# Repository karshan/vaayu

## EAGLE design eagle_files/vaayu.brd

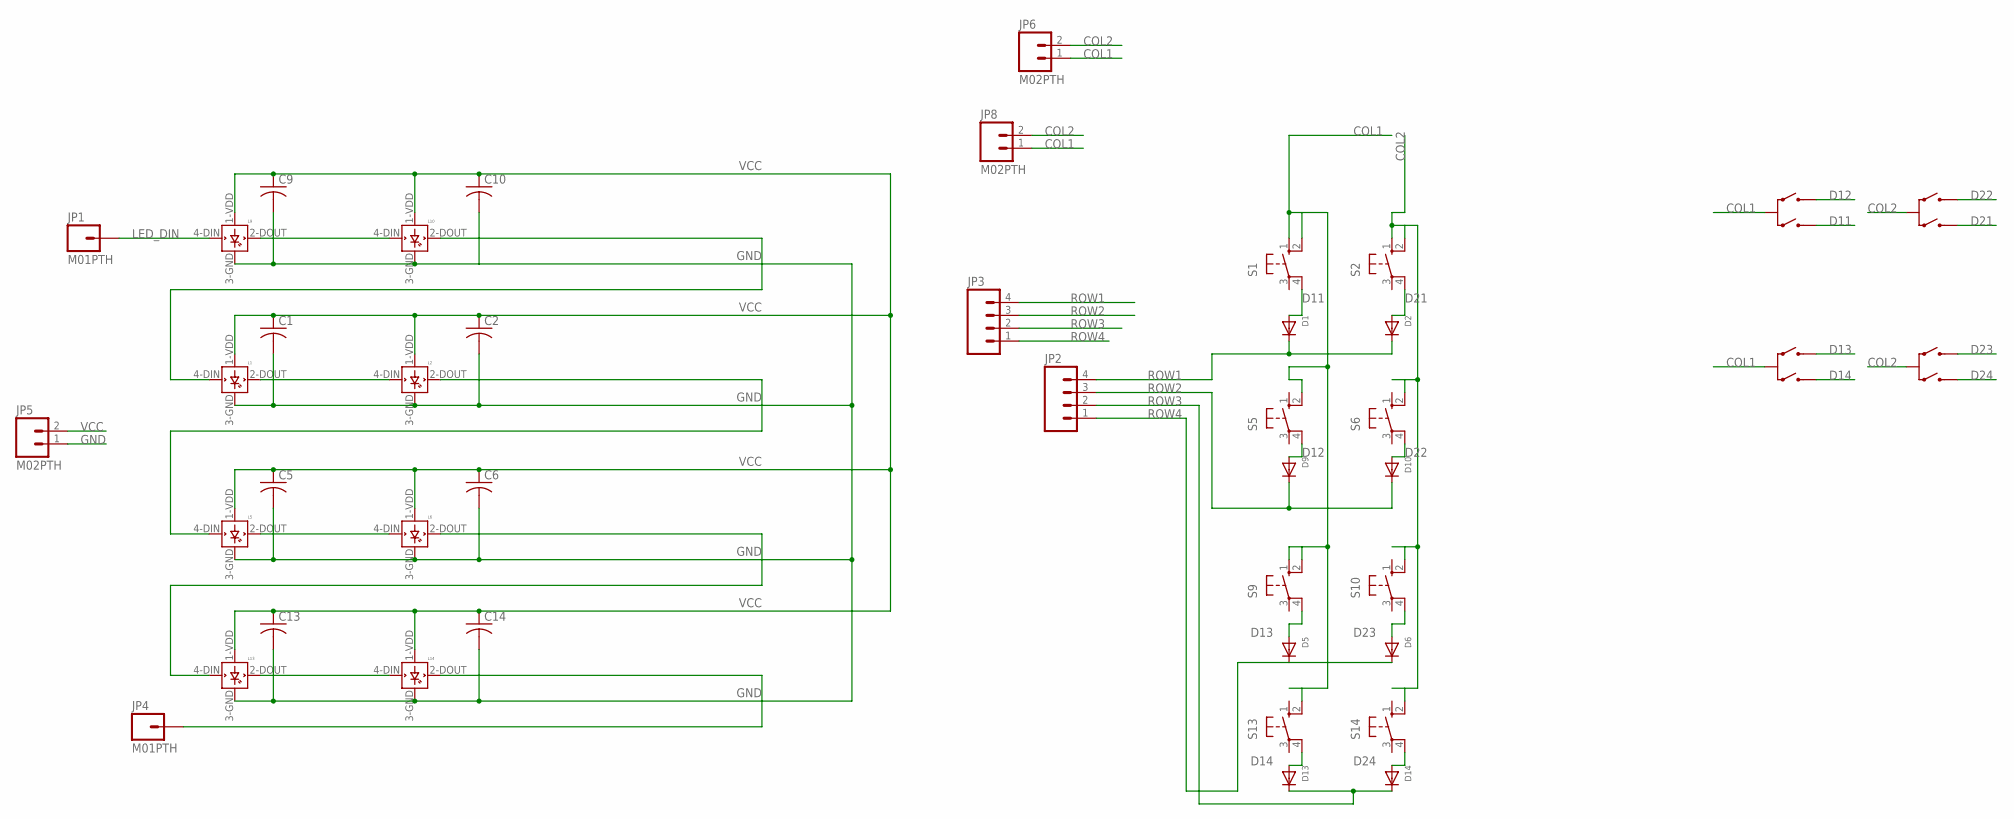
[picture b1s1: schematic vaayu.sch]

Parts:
C1, C2, C5, C6, C9, C10, C13, C14: C-USC1206; C1206
D1, D2, D5, D6, D9, D10, D13, D14: DIODESOD-123; SOD-123
JP1, JP4: M01PTH; 1X01
JP2, JP3: M04PTH; 1X04
JP5, JP6, JP8: M02PTH; 1X02
L1, L2, L5, L6, L9, L10, L13, L14: WS2812B
S1, S2, S5, S6, S9, S10, S13, S14: 10-XX; B3F-10XX
U$1, U$4, U$5, U$8: ALPHA-ROT-ENCODER; TW-700198

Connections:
COL1: JP6.1, JP8.1, S1.1 (S), S1.2 (S1), S5.2 (S1), S9.1 (S), S9.2 (S1), S13.2 (S1), U$4.P2 (COM), U$8.P2 (COM)
COL2: JP6.2, JP8.2, S2.1 (S), S2.2 (S1), S6.2 (S1), S10.2 (S1), S14.2 (S1), U$1.P2 (COM), U$5.P2 (COM)
D11: D1.A, S1.4 (P1), U$4.P1 (B)
D12: D9.A, S5.4 (P1), U$4.P3 (A)
D13: D5.A, S9.4 (P1), U$8.P3 (A)
D14: D13.A, S13.4 (P1), U$8.P1 (B)
D21: D2.A, S2.4 (P1), U$1.P1 (B)
D22: D10.A, S6.4 (P1), U$1.P3 (A)
D23: D6.A, S10.4 (P1), U$5.P3 (A)
D24: D14.A, S14.4 (P1), U$5.P1 (B)
GND: C1.2, C2.2, C5.2, C6.2, C9.2, C10.2, C13.2, C14.2, JP5.1, L1.3-GND (GND), L2.3-GND (GND), L5.3-GND (GND), L6.3-GND (GND), L9.3-GND (GND), L10.3-GND (GND), L13.3-GND (GND), L14.3-GND (GND)
LED_DIN: JP1.1, L9.4-DIN (DIN)
unnamed: L1.2-DOUT (DOUT), L2.4-DIN (DIN)
unnamed: L2.2-DOUT (DOUT), L5.4-DIN (DIN)
unnamed: L5.2-DOUT (DOUT), L6.4-DIN (DIN)
unnamed: L6.2-DOUT (DOUT), L13.4-DIN (DIN)
unnamed: L13.2-DOUT (DOUT), L14.4-DIN (DIN)
unnamed: JP4.1, L14.2-DOUT (DOUT)
unnamed: L9.2-DOUT (DOUT), L10.4-DIN (DIN)
unnamed: L1.4-DIN (DIN), L10.2-DOUT (DOUT)
ROW1: D1.C, D2.C, JP2.4, JP3.4
ROW2: D9.C, D10.C, JP2.3, JP3.3
ROW3: D13.C, D14.C, JP2.2, JP3.2
ROW4: D5.C, D6.C, JP2.1, JP3.1
VCC: C1.1, C2.1, C5.1, C6.1, C9.1, C10.1, C13.1, C14.1, JP5.2, L1.1-VDD (VDD), L2.1-VDD (VDD), L5.1-VDD (VDD), L6.1-VDD (VDD), L9.1-VDD (VDD), L10.1-VDD (VDD), L13.1-VDD (VDD), L14.1-VDD (VDD)

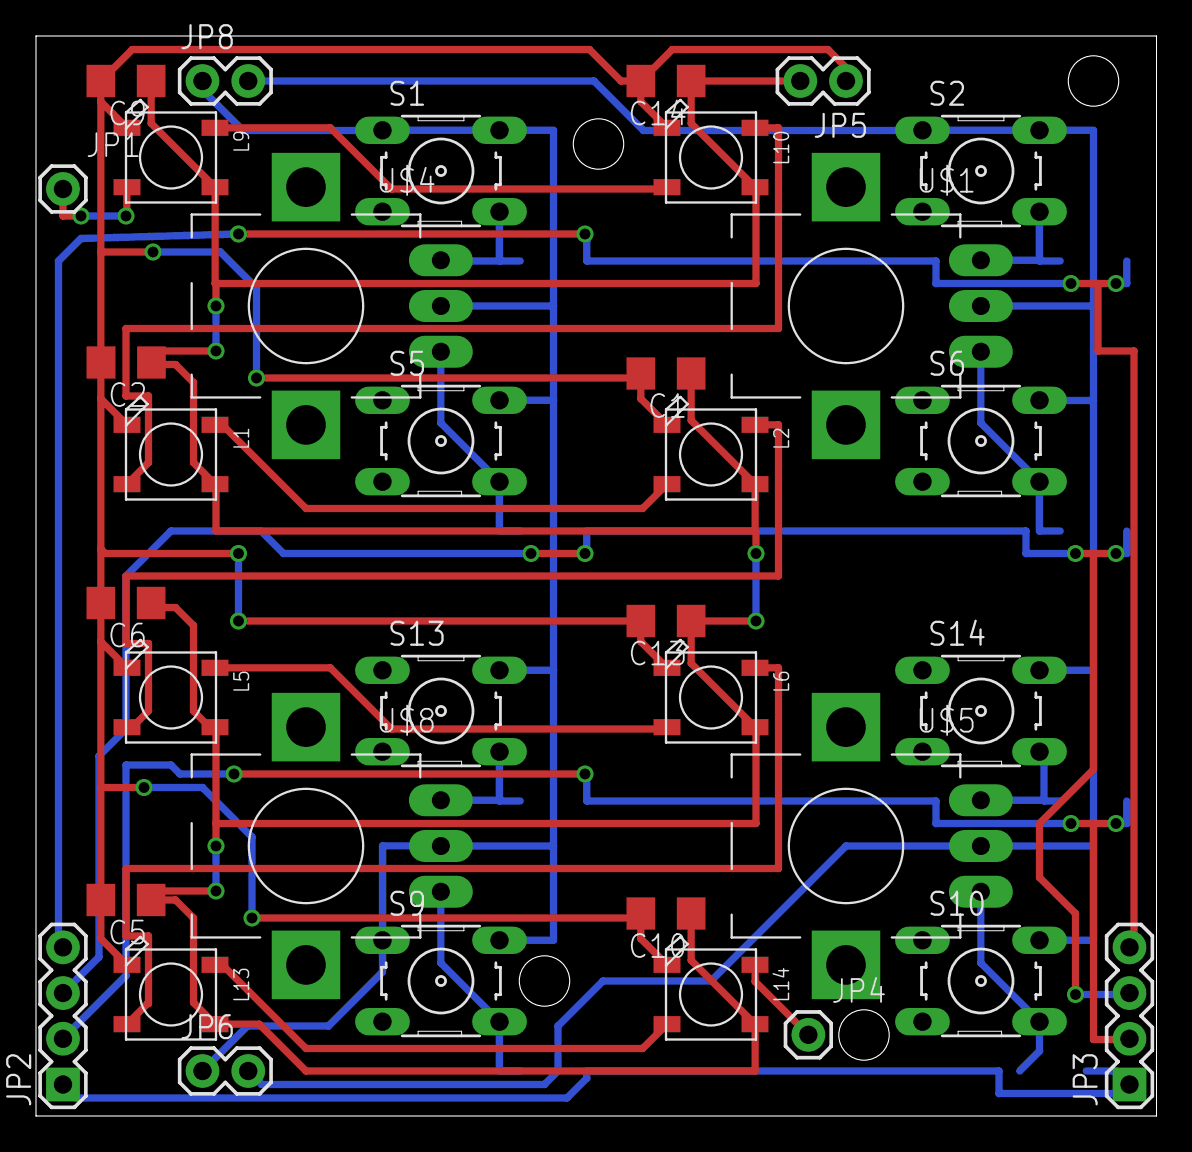
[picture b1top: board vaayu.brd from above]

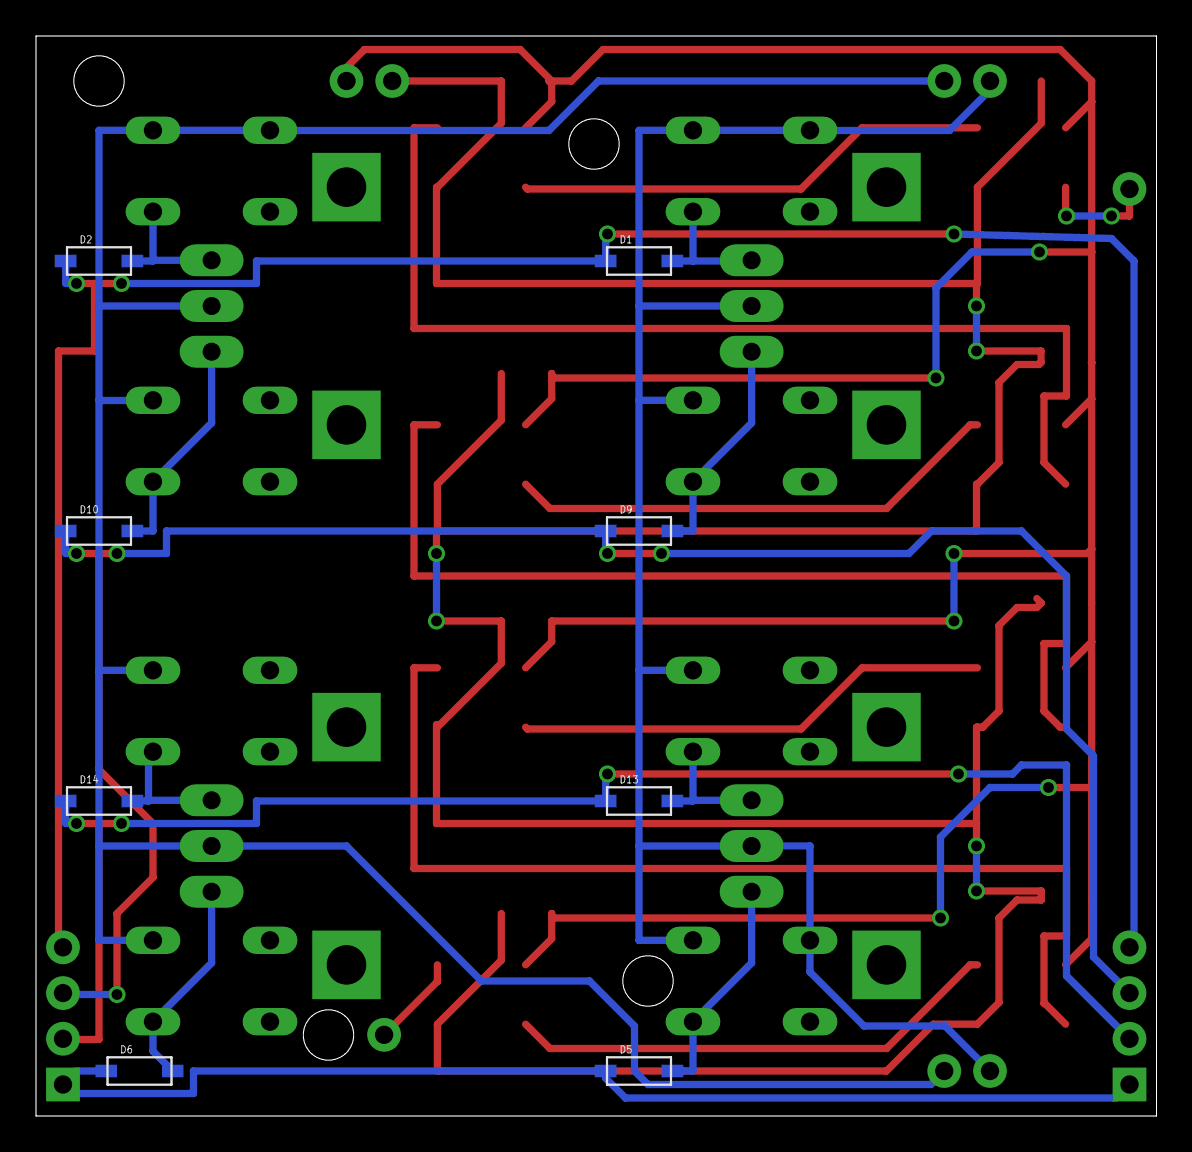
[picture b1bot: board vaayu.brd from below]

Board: 2 copper layers, 62.2 x 60.0 mm, 43 parts (8 on the bottom side), 25 nets.

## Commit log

2015-12-13 inital commit
2015-12-14 working commit
2015-12-14 missing app.c :S
2015-12-14 working commit for reals
2015-12-14 implement colors of leds according to encoder output
2015-12-14 more obvious colors
2015-12-14 implemented code for new button board, some buttons appear not to work
2015-12-14 button leds blink when pressed
2015-12-14 add faceplate design
2015-12-14 added 3d grid generator
2015-12-14 added the actual board file :S
2016-01-30 SYSEX -> LED setting
    - also some case design stuff i worked on a while ago, pretty useless
    - add arm-...-gcc to path in env.sh
2016-01-30 fix rgb snake
2016-01-30 Fixed RGB snake by disabling interrupts
2016-02-06 Add controller script
2016-07-05 Clean rewrite for new 8x16 board
    - LEDs tested
    - need to switch outputs to Open Drain mode and add 5v pullups to outputs to test buttons
2016-10-12 32 CC's with colorwheel one button for sensitivity
2017-08-09 as is

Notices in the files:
parts and their libraries:
SparkFun-Connectors: Licensing: Creative Commons ShareAlike 4.0 International - https://creativecommons.org/licenses/by-sa/4.0
